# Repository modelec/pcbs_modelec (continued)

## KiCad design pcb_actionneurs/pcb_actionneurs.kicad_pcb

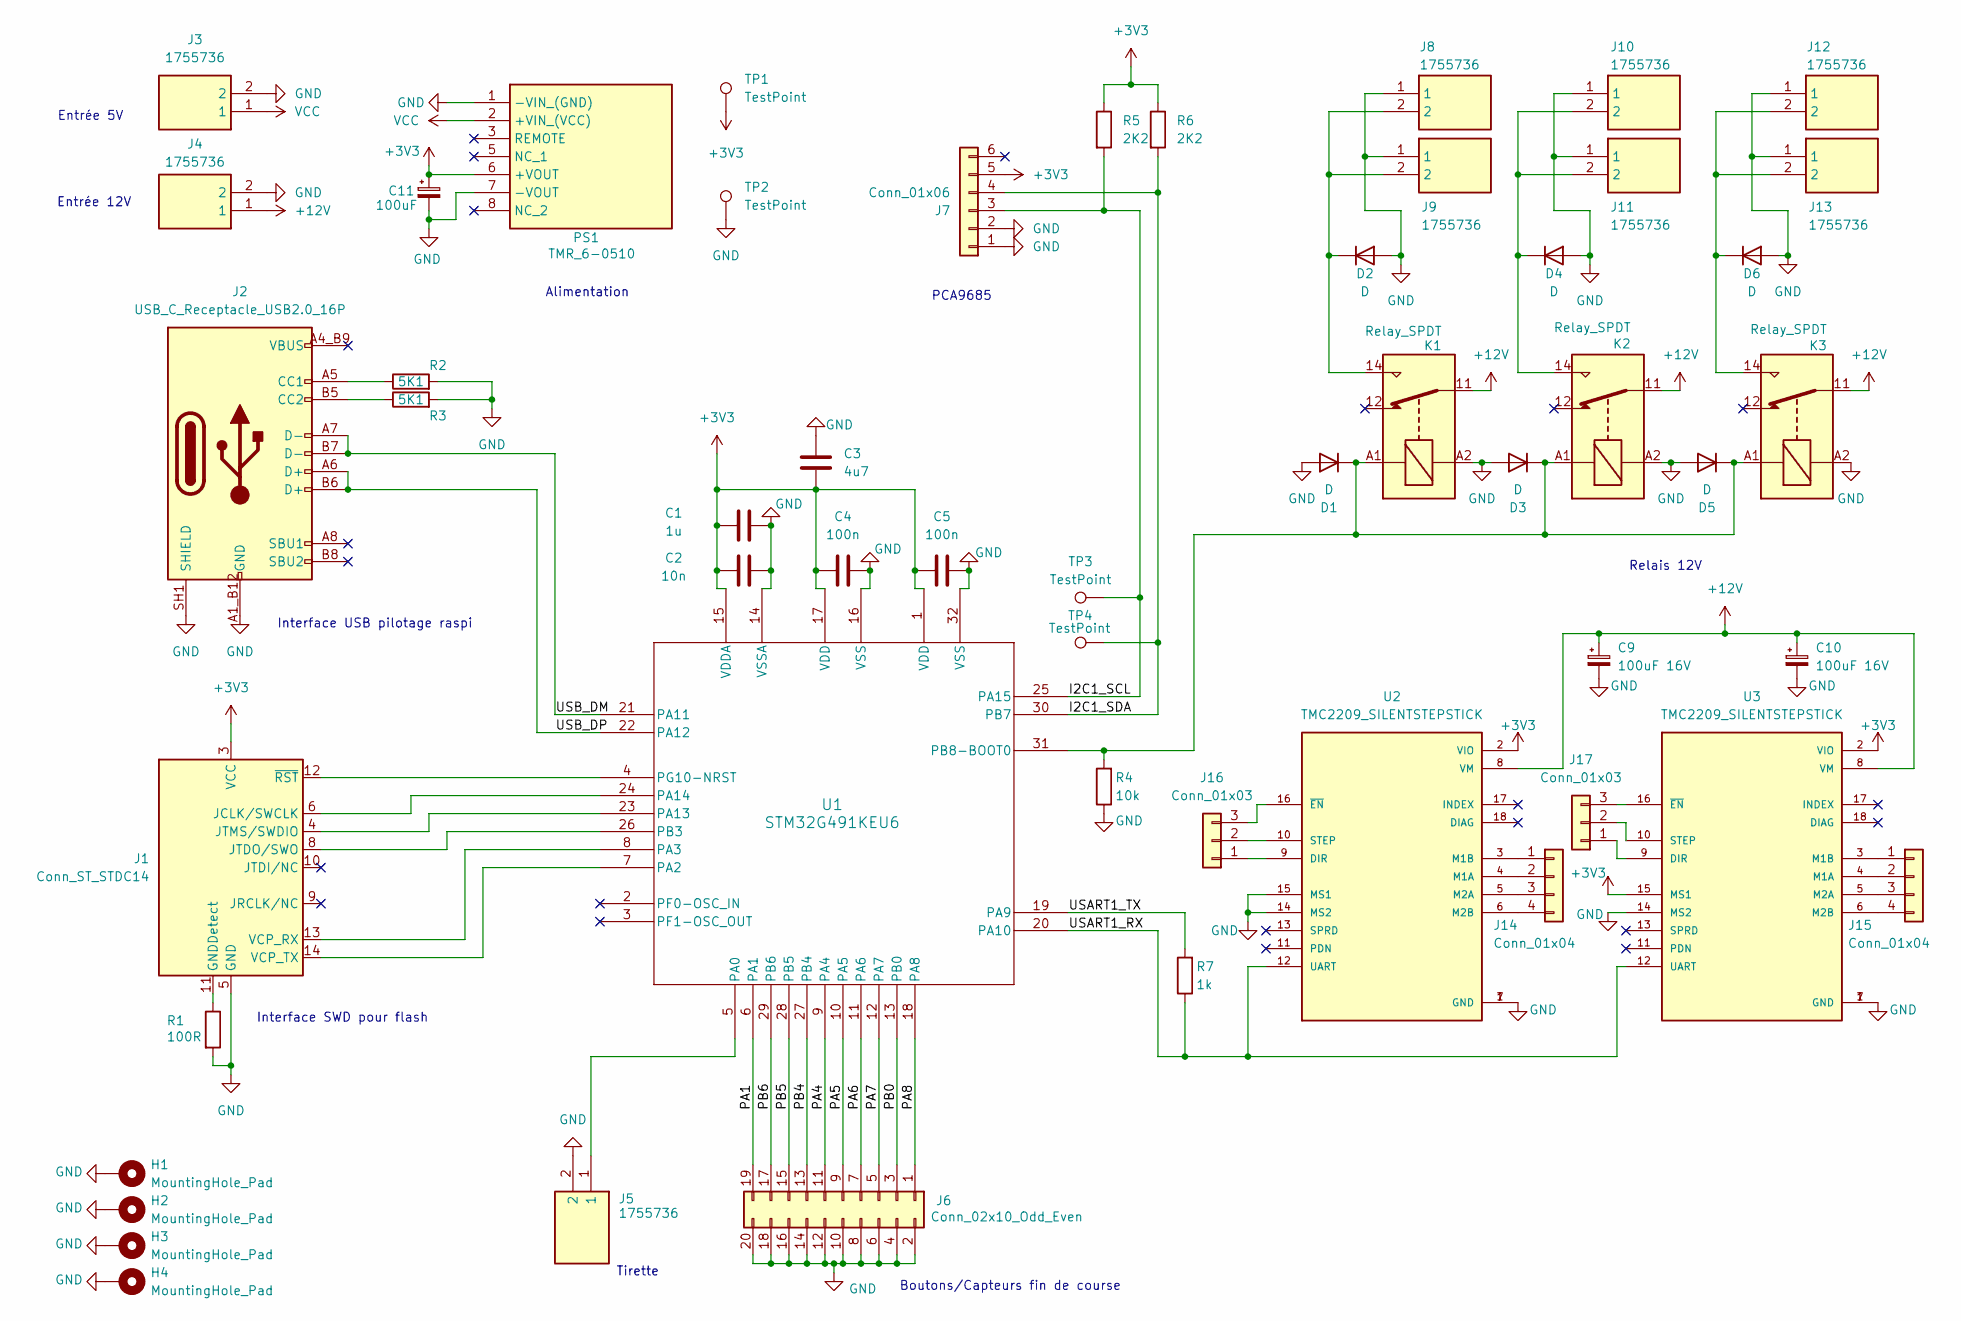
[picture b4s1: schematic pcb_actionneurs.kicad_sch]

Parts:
C1: 1u; C_0805_2012Metric_Pad1.18x1.45mm_HandSolder; Manufacturer_Part_Number VJ0805Y105KXQTW1BC
C2: 10n; C_0805_2012Metric_Pad1.18x1.45mm_HandSolder; Manufacturer_Part_Number VJ0805Y103KXAMC
C3: 4u7; C_0805_2012Metric_Pad1.18x1.45mm_HandSolder; Manufacturer_Part_Number VJ0805G475KXQTW1BC
C4, C5: 100n; C_0805_2012Metric_Pad1.18x1.45mm_HandSolder; Manufacturer_Part_Number VJ0805Y104KXAMR
C9, C10: 100uF 16V; CP_6.3x11mm_horiz-L
C11: 100uF; C_Radial_D6.3mm_H11.0mm_P2.50mm
D1, D2, D3, D4, D5, D6: D; D_DO-35_SOD27_P7.62mm_Horizontal
H1, H2, H3, H4: MountingHole_Pad; MountingHole_3.2mm_M3_ISO14580_Pad_TopBottom
J1: Conn_ST_STDC14; CONN14_3220-14_CNC; Manufacturer_Part_Number 3220-14-0100-00
J2: USB_C_Receptacle_USB2.0_16P; GCT_USB4105-GF-A
J3, J4, J5, J8, J9, J10, J11, J12, J13: 1755736; PhoenixContact_MSTBVA_2,5_2-G-5,08_1x02_P5.08mm_Vertical; Manufacturer_Part_Number 1755736; Mouser Part Number 651-1755736
J6: Conn_02x10_Odd_Even; PinHeader_2x10_P2.54mm_Vertical
J7: Conn_01x06; PinHeader_1x06_P2.54mm_Vertical
J14, J15: Conn_01x04; PinHeader_1x04_P2.54mm_Vertical
J16, J17: Conn_01x03; PinHeader_1x03_P2.54mm_Vertical
K1, K2, K3: Relay_SPDT; Relay_SPDT_Finder_36.11
PS1: TMR_6-0510; TMR60510; Manufacturer_Part_Number TMR 6-0510; Mouser Part Number 495-TMR6-0510
R1: 100R; R_0805_2012Metric_Pad1.20x1.40mm_HandSolder; Manufacturer_Part_Number CRCW0805100RFKEA
R2, R3: 5K1; R_0805_2012Metric_Pad1.20x1.40mm_HandSolder
R4: 10k; R_0805_2012Metric_Pad1.20x1.40mm_HandSolder; Manufacturer_Part_Number CRCW080510K0FKEA
R5, R6: 2K2; R_0805_2012Metric_Pad1.20x1.40mm_HandSolder
R7: 1k; R_0805_2012Metric_Pad1.20x1.40mm_HandSolder; Manufacturer_Part_Number CRCW080510K0FKEA
TP1, TP2, TP3, TP4: TestPoint; TestPoint_Bridge_Pitch2.54mm_Drill0.7mm
U1: STM32G491KEU6
U2, U3: TMC2209_SILENTSTEPSTICK; MODULE_TMC2209_SILENTSTEPSTICK; PARTREV 1.20

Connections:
+3V3: C1.1, C2.1, C3.1, C4.1, C5.1, C11.1, J1.3 (VCC), J7.5, PS1.6 (+VOUT), R5.1, R6.1, TP1.1, U1.1 (VDD), U1.15 (VDDA), U1.17 (VDD), U2.2 (VIO), U3.2 (VIO), U3.15 (MS1)
+12V: C9.1, C10.1, J4.1, K1.11, K2.11, K3.11, U2.8 (VM), U3.8 (VM)
/I2C1_SCL: J7.3, R5.2, TP3.1, U1.25 (PA15)
/I2C1_SDA: J7.4, R6.2, TP4.1, U1.30 (PB7)
/PA1: J6.19, U1.6 (PA1)
/PA4: J6.11, U1.9 (PA4)
/PA5: J6.9, U1.10 (PA5)
/PA6: J6.7, U1.11 (PA6)
/PA7: J6.5, U1.12 (PA7)
/PA8: J6.1, U1.18 (PA8)
/PB0: J6.3, U1.13 (PB0)
/PB4: J6.13, U1.27 (PB4)
/PB5: J6.15, U1.28 (PB5)
/PB6: J6.17, U1.29 (PB6)
/USART1_RX: R7.1, U1.20 (PA10), U2.12 (UART), U3.12 (UART)
/USART1_TX: R7.2, U1.19 (PA9)
/USB_DM: J2.A7 (D-), J2.B7 (D-), U1.21 (PA11)
/USB_DP: J2.A6 (D+), J2.B6 (D+), U1.22 (PA12)
GND: C1.2, C2.2, C3.2, C4.2, C5.2, C9.2, C10.2, C11.2, D1.2 (A), D2.2 (A), D3.2 (A), D4.2 (A), D5.2 (A), D6.2 (A), H1.1, H2.1, H3.1, H4.1, J1.5 (GND), J1.7 (GND), J2.A1_B12 (GND), J2.B1_A12 (GND), J2.SH1 (SHIELD), J2.SH2, J2.SH3, J2.SH4, J3.2, J4.2, J5.2, J6.2, J6.4, J6.6, J6.8, J6.10, J6.12, J6.14, J6.16, J6.18, J6.20, J7.1, J7.2, J8.1, J9.1, J10.1, J11.1, J12.1, J13.1, K1.A2, K2.A2, K3.A2, PS1.1 (-VIN_(GND)), PS1.7 (-VOUT), R1.2, R2.2, R3.2, R4.1, TP2.1, U1.14 (VSSA), U1.16 (VSS), U1.32 (VSS), U2.1 (GND), U2.7 (GND), U2.14 (MS2), U2.15 (MS1), U3.1 (GND), U3.7 (GND), U3.14 (MS2)
unnamed: D1.1 (K), D3.1 (K), D5.1 (K), K1.A1, K2.A1, K3.A1, R4.2, U1.31 (PB8-BOOT0)
unnamed: D2.1 (K), J8.2, J9.2, K1.14
unnamed: D4.1 (K), J10.2, J11.2, K2.14
unnamed: D6.1 (K), J12.2, J13.2, K3.14
unnamed: J1.11 (GNDDetect), R1.1
unnamed: J1.6 (JCLK/SWCLK), U1.24 (PA14)
unnamed: J1.8 (JTDO/SWO), U1.26 (PB3)
unnamed: J1.4 (JTMS/SWDIO), U1.23 (PA13)
unnamed: J1.13 (VCP_RX), U1.8 (PA3)
unnamed: J1.14 (VCP_TX), U1.7 (PA2)
unnamed: J1.12 (~RST), U1.4 (PG10-NRST)
unnamed: J2.A5 (CC1), R2.1
unnamed: J2.B5 (CC2), R3.1
unnamed: J14.1, U2.3 (M1B)
unnamed: J14.2, U2.4 (M1A)
unnamed: J14.3, U2.5 (M2A)
unnamed: J14.4, U2.6 (M2B)
unnamed: J15.1, U3.3 (M1B)
unnamed: J15.2, U3.4 (M1A)
unnamed: J15.3, U3.5 (M2A)
unnamed: J15.4, U3.6 (M2B)
unnamed: J16.1, U2.9 (DIR)
unnamed: J16.2, U2.10 (STEP)
unnamed: J16.3, U2.16 (~EN)
unnamed: J17.1, U3.9 (DIR)
unnamed: J17.2, U3.10 (STEP)
unnamed: J17.3, U3.16 (~EN)
unnamed: J5.1, U1.5 (PA0)
VCC: J3.1, PS1.2 (+VIN_(VCC))

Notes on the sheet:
Entrée 5V
PCA9685
Relais 12V
Interface SWD pour flash
Entrée 12V
Boutons/Capteurs fin de course
Tirette
Alimentation
Interface USB pilotage raspi

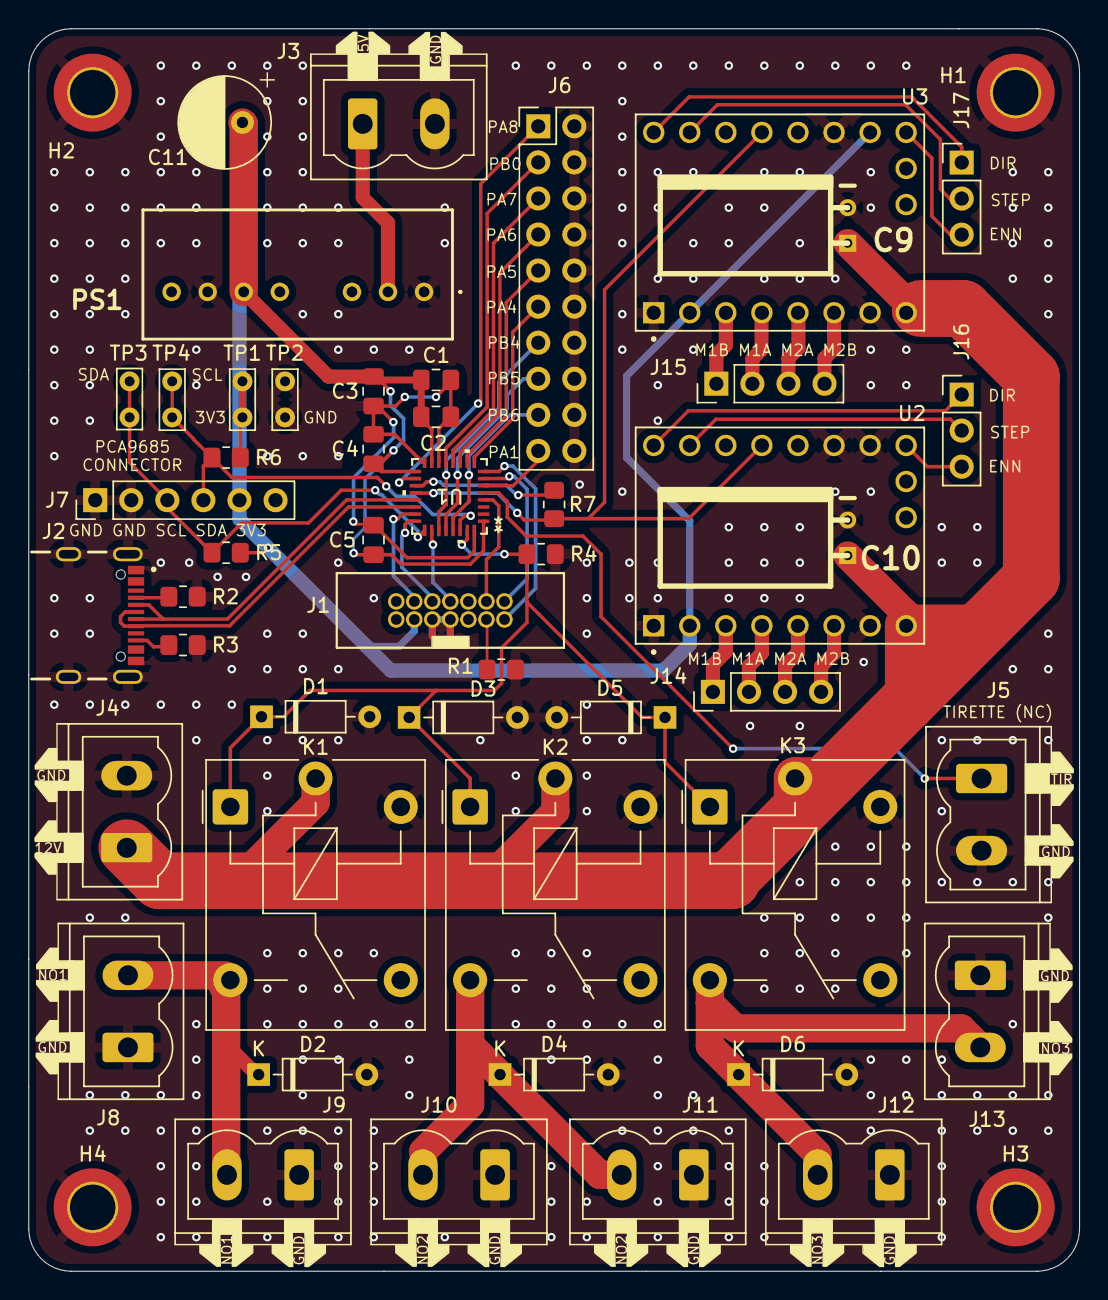
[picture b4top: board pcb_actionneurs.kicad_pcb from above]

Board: 2 copper layers, 74.0 x 87.5 mm, 53 parts (0 on the bottom side), 48 nets.

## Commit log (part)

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2025-03-06 work on power supply
2025-03-06 dernieres retouches suite changement de repo
2025-03-07 fix: decouplage esp32
2025-03-08 dernieres retourches pcb alim
2025-03-11 feat: add usb port + add RESET button
2025-03-12 feat: add cp2102 usb to uart + auto flash circuit
2025-03-13 feat: cp2102 usb to uart
2025-03-13 correction alim PAMI et travail odo (WIP)
2025-03-19 PCB odometrie schema fini
2025-03-19 ajout commentaire pcb odo
2025-03-20 ajout TMC2209
2025-03-21 drivers moteurs pap pamis
2025-03-21 ajout des connexions entre le circuit des moteurs pas à pas et l'ESP32
2025-03-22 ajout bouton arrêt d'urgence
2025-03-22 routage pcb odométrie fait : reste quelques reglages pour s'adapter au DBH-12
2025-03-23 changement pin encodeur pour avoir la fonction timer
2025-03-23 connecteur 14pin avec detrompage + renumerotation TOF
2025-03-24 version finale PCB odometrie
2025-03-25 ajustement pos pins pcb odometrie + 3 batteries et TODOs sur le schema pcb pamis
2025-03-30 ajout d'un connecteur pour les GPIO restant
2025-04-06 Ajout connecteurs, diodes sur arrêt moteurs et finalisation du schéma
2025-04-07 ajout des empreintes pour le pcb PAMI
2025-04-07 finalisation empreintes des composants
2025-04-09 remplacement usb A par type C sur schéma PAMI pour une meilleure cohérence avec le PCB
2025-04-10 correction symbole type C
2025-04-10 wip: placement composants
2025-04-11 premier placement des composants sur le pcb PAMI
2025-04-11 plan de masse sur pcb pamis et ajout projet pcb actionneurs
2025-04-12 ajustements et optimisations du placement des composants sur PCB Pami
2025-04-12 miniaturisation PCB Pami
2025-04-12 ajout fixations
2025-04-14 début routage PCB Pami
2025-04-14 v1 routage
2025-04-15 routage avec 4 couches
2025-04-16 ajout indications
2025-04-16 legeres retouches, plan gnd couche top/bottom et suppression angles droits
2025-04-17 suppression vias GND inutiles + ajout logo modelec
2025-04-17 mise à jour des chemins pour le modèle 3D de la lib modelec
2025-04-17 mise à jour modèle 3D empreintes dans le projet PAMI
2025-04-18 ajout texte PCB Pami
2025-04-24 ajout mesures
2025-04-24 premier jet routage pcb actionneurs, encore des choses à faire
2025-04-29 commencement correctifs PCB Pami
2025-04-30 nouveau placement -suite
2025-05-01 finalisation nouveau routage
2025-05-01 matrice de vias PCB Pami
2025-05-02 déplacement fusible
2025-05-05 plein de choses que j'avais pas sauvegardé
2025-05-06 Ajout empreinte condo couché + réparation contour PCB avec 7mm autour des trous de fixation
2025-05-09 dernières corrections PCB PAMIS
2025-05-10 Ajout BAU servo PAMI, finitions PCB Actionneurs, fichier fab stencil. Version commandée PAMI & Actionneurs
2025-05-22 correctif auto flash pcb pami
